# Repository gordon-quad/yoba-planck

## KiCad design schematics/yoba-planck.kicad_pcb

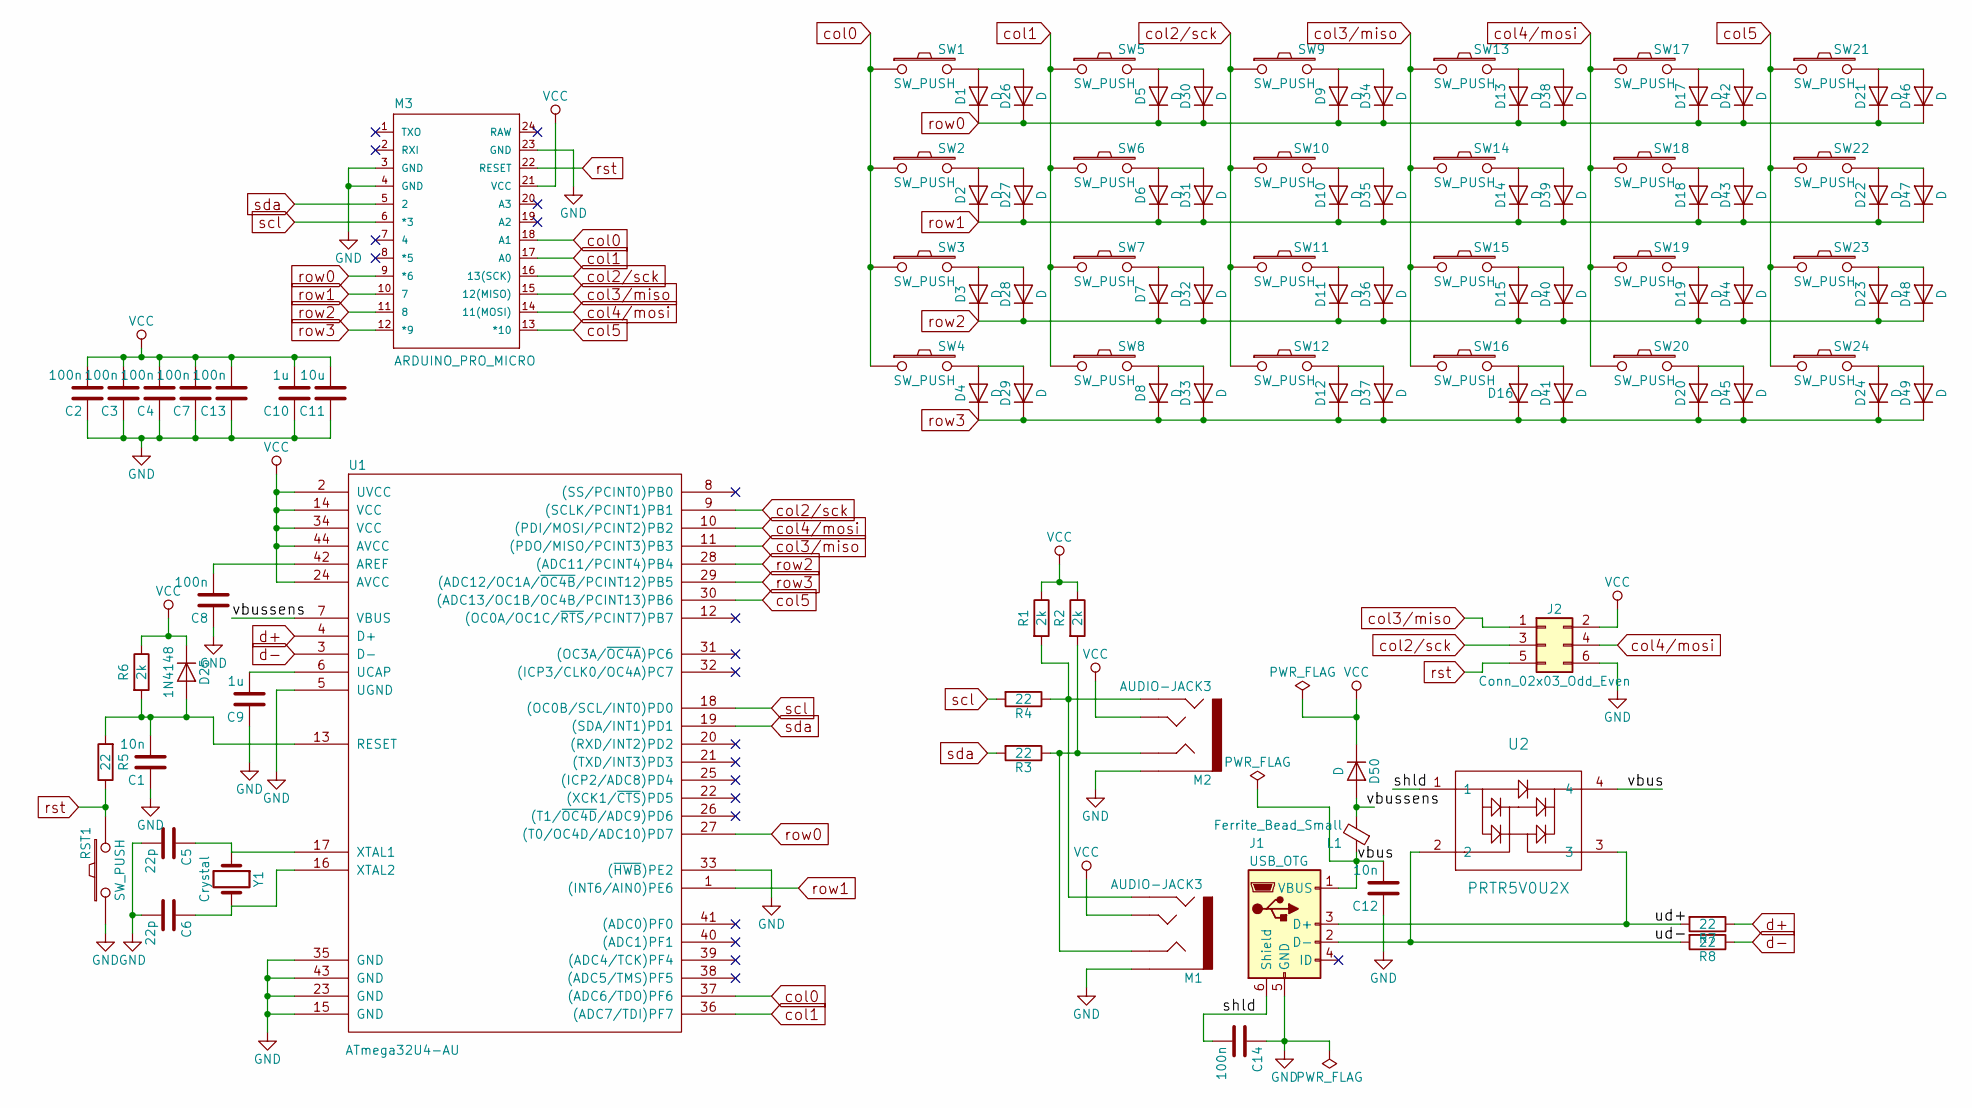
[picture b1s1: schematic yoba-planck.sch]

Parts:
C1, C12: 10n; C_0603_HandSoldering
C2, C3, C4, C7, C8, C13, C14: 100n; C_0603_HandSoldering
C5, C6: 22p; C_0603_HandSoldering
C9, C10: 1u; C_0603_HandSoldering
C11: 10u; C_0805_HandSoldering
D1, D2, D3, D4, D5, D6, D7, D8, D9, D10, D11, D12, D13, D14, D15, D16, D17, D18, D19, D20, D21, D22, D23, D24: D; Diode_DO-35_SOD27_Horizontal_RM10
D25: 1N4148; SOD-123
D26, D27, D28, D29, D30, D31, D32, D33, D34, D35, D36, D37, D38, D39, D40, D41, D42, D43, D44, D45, D46, D47, D48, D49, D50: D; SOD-123
J1: USB_OTG; USB_Micro-B_10103594-0001LF
J2: Conn_02x03_Odd_Even; Pin_Header_Straight_2x03
L1: Ferrite_Bead_Small; C_0603_HandSoldering
M1, M2: AUDIO-JACK3; TRRS-ebay
M3: ARDUINO_PRO_MICRO
R1, R2: 2k; Resistor_SMDuniversal_0805to1206_HandSoldering
R3, R4: 22; Resistor_SMDuniversal_0805to1206_HandSoldering
R5, R7, R8: 22; R_0603_HandSoldering
R6: 2k; R_0603_HandSoldering
RST1: SW_PUSH; edgeswbut
SW1, SW2, SW3, SW4, SW5, SW6, SW7, SW8, SW9, SW10, SW11, SW12, SW13, SW14, SW15, SW16, SW17, SW18, SW19, SW20, SW21, SW22, SW23, SW24: SW_PUSH; MX1A
U1: ATmega32U4-AU; TQFP-44_10x10mm_Pitch0.8mm
U2: PRTR5V0U2X; SOT143B
Y1: Crystal; Crystal_SMD_5032_2Pads

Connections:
/shld: C14.2, J1.6 (Shield), U2.1
/ud+: J1.3 (D+), R7.2, U2.3
/ud-: J1.2 (D-), R8.2, U2.2
/vbus: C12.2, J1.1 (VBUS), L1.1, U2.4
/vbussens: D50.2 (A), L1.2, U1.7 (VBUS)
GND: C1.1, C2.1, C3.1, C4.1, C5.2, C6.2, C7.1, C8.1, C9.1, C10.1, C11.1, C12.1, C13.1, C14.1, J1.5 (GND), J2.6, M1.1 (EARTH), M2.1 (EARTH), M3.3 (GND), M3.4 (GND), M3.23 (GND), RST1.1, U1.5 (UGND), U1.15 (GND), U1.23 (GND), U1.33 ((~HWB~)PE2), U1.35 (GND), U1.43 (GND)
unnamed: C1.2, D25.2 (A), R5.2, R6.2, U1.13 (RESET)
unnamed: C5.1, U1.17 (XTAL1), Y1.1
unnamed: C6.1, U1.16 (XTAL2), Y1.2
unnamed: C8.2, U1.42 (AREF)
unnamed: C9.2, U1.6 (UCAP)
unnamed: D1.2 (A), D26.2 (A), SW1.2
unnamed: D2.2 (A), D27.2 (A), SW2.2
unnamed: D10.2 (A), D35.2 (A), SW10.2
unnamed: D11.2 (A), D36.2 (A), SW11.2
unnamed: D12.2 (A), D37.2 (A), SW12.2
unnamed: D13.2 (A), D38.2 (A), SW13.2
unnamed: D14.2 (A), D39.2 (A), SW14.2
unnamed: D15.2 (A), D40.2 (A), SW15.2
unnamed: D16.2 (A), D41.2 (A), SW16.2
unnamed: D17.2 (A), D42.2 (A), SW17.2
unnamed: D18.2 (A), D43.2 (A), SW18.2
unnamed: D19.2 (A), D44.2 (A), SW19.2
unnamed: D20.2 (A), D45.2 (A), SW20.2
unnamed: D21.2 (A), D46.2 (A), SW21.2
unnamed: D22.2 (A), D47.2 (A), SW22.2
unnamed: D23.2 (A), D48.2 (A), SW23.2
unnamed: D24.2 (A), D49.2 (A), SW24.2
unnamed: D3.2 (A), D28.2 (A), SW3.2
unnamed: D4.2 (A), D29.2 (A), SW4.2
unnamed: D5.2 (A), D30.2 (A), SW5.2
unnamed: D6.2 (A), D31.2 (A), SW6.2
unnamed: D7.2 (A), D32.2 (A), SW7.2
unnamed: D8.2 (A), D33.2 (A), SW8.2
unnamed: D9.2 (A), D34.2 (A), SW9.2
unnamed: M1.2 (RNG2), M2.2 (RNG2), R1.2, R4.1
unnamed: M1.3 (RNG1), M2.3 (RNG1), R2.2, R3.1
VCC: C2.2, C3.2, C4.2, C7.2, C10.2, C11.2, C13.2, D25.1 (K), D50.1 (K), J2.2, M1.4 (TIP), M2.4 (TIP), M3.21 (VCC), R1.1, R2.1, R6.1, U1.2 (UVCC), U1.14 (VCC), U1.24 (AVCC), U1.34 (VCC), U1.44 (AVCC)
col0: M3.18 (A1), SW1.1, SW2.1, SW3.1, SW4.1, U1.37 ((ADC6/TDO)PF6)
col1: M3.17 (A0), SW5.1, SW6.1, SW7.1, SW8.1, U1.36 ((ADC7/TDI)PF7)
col2/sck: J2.3, M3.16 (13(SCK)), SW9.1, SW10.1, SW11.1, SW12.1, U1.9 ((SCLK/PCINT1)PB1)
col3/miso: J2.1, M3.15 (12(MISO)), SW13.1, SW14.1, SW15.1, SW16.1, U1.11 ((PDO/MISO/PCINT3)PB3)
col4/mosi: J2.4, M3.14 (11(MOSI)), SW17.1, SW18.1, SW19.1, SW20.1, U1.10 ((PDI/MOSI/PCINT2)PB2)
col5: M3.13 (*10), SW21.1, SW22.1, SW23.1, SW24.1, U1.30 ((ADC13/OC1B/OC4B/PCINT13)PB6)
d+: R7.1, U1.4 (D+)
d-: R8.1, U1.3 (D-)
row0: D1.1 (K), D5.1 (K), D9.1 (K), D13.1 (K), D17.1 (K), D21.1 (K), D26.1 (K), D30.1 (K), D34.1 (K), D38.1 (K), D42.1 (K), D46.1 (K), M3.9 (*6), U1.27 ((T0/OC4D/ADC10)PD7)
row1: D2.1 (K), D6.1 (K), D10.1 (K), D14.1 (K), D18.1 (K), D22.1 (K), D27.1 (K), D31.1 (K), D35.1 (K), D39.1 (K), D43.1 (K), D47.1 (K), M3.10 (7), U1.1 ((INT6/AIN0)PE6)
row2: D3.1 (K), D7.1 (K), D11.1 (K), D15.1 (K), D19.1 (K), D23.1 (K), D28.1 (K), D32.1 (K), D36.1 (K), D40.1 (K), D44.1 (K), D48.1 (K), M3.11 (8), U1.28 ((ADC11/PCINT4)PB4)
row3: D4.1 (K), D8.1 (K), D12.1 (K), D16.1 (K), D20.1 (K), D24.1 (K), D29.1 (K), D33.1 (K), D37.1 (K), D41.1 (K), D45.1 (K), D49.1 (K), M3.12 (*9), U1.29 ((ADC12/OC1A/~OC4B~/PCINT12)PB5)
rst: J2.5, M3.22 (RESET), R5.1, RST1.2
scl: M3.6 (*3), R4.2, U1.18 ((OC0B/SCL/INT0)PD0)
sda: M3.5 (2), R3.2, U1.19 ((SDA/INT1)PD1)

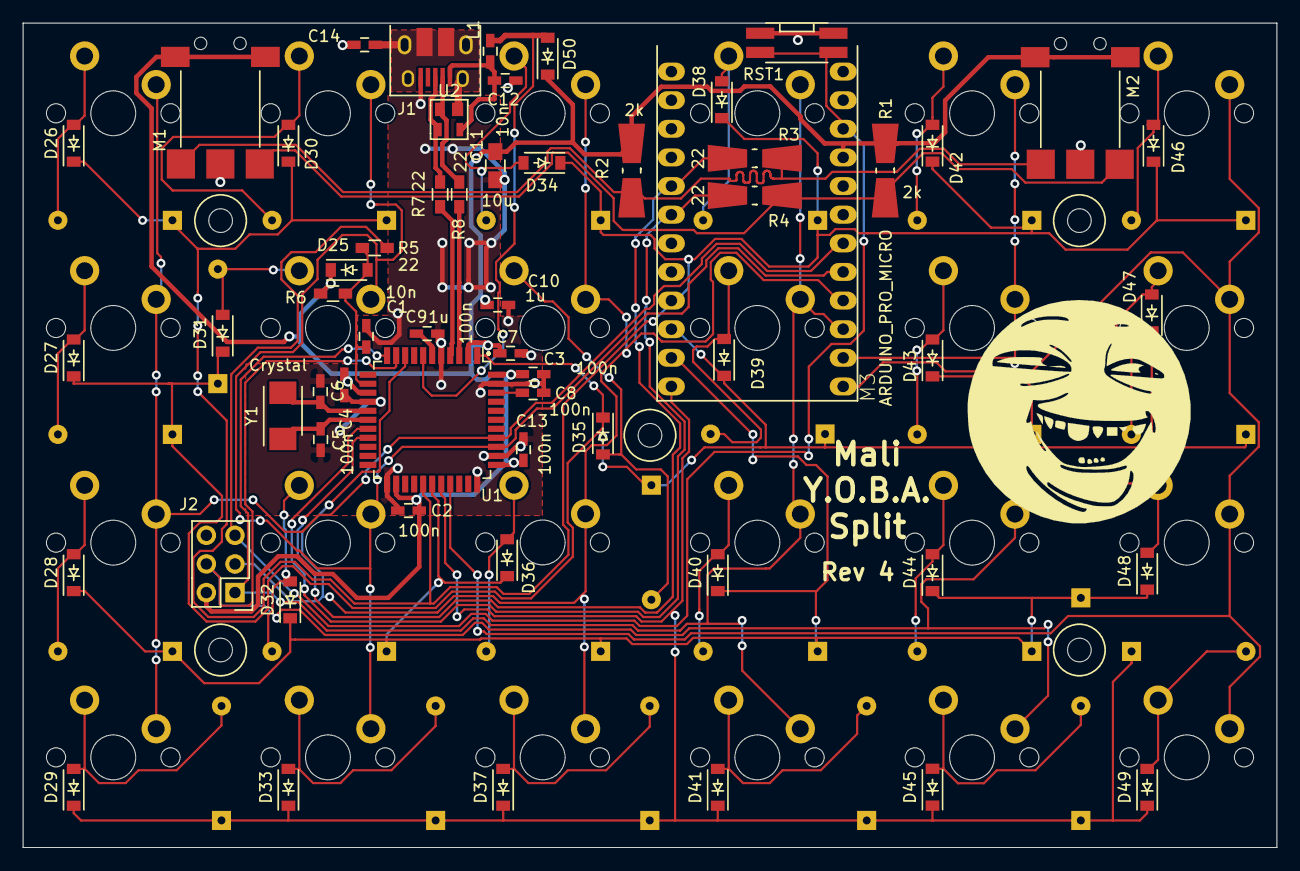
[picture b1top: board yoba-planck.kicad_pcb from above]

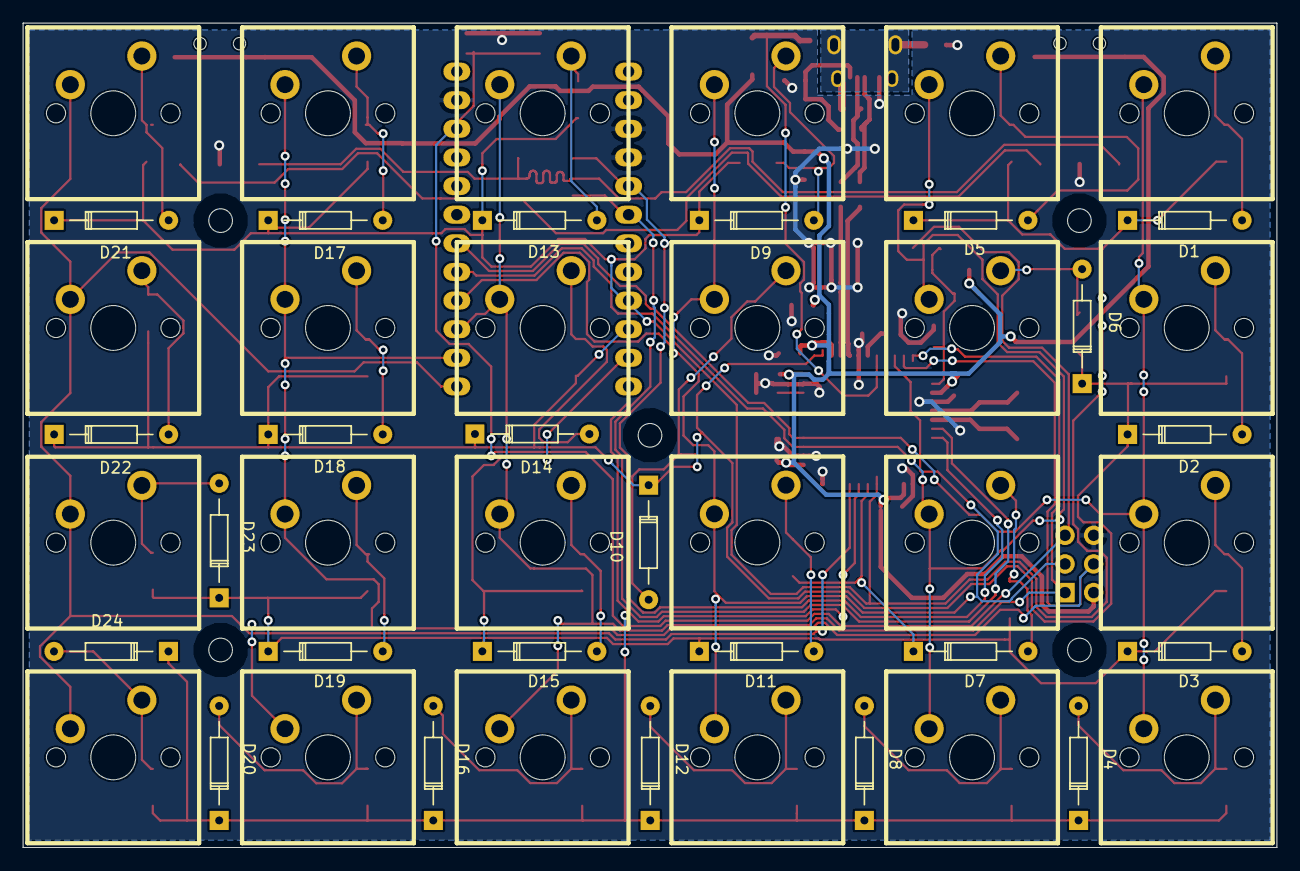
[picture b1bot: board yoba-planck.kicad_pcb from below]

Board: 2 copper layers, 111.2 x 73.2 mm, 106 parts (48 on the bottom side), 53 nets.

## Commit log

2017-03-29 removed silk screen outside board edges
2017-03-29 series resistance added to i2c bus
2017-03-30 Logo updated, layout improoved, mouting holes enlarged
2017-03-30 fixed board outline
2017-05-20 rev2
2017-05-20 case added
2018-02-25 yoba rev3 to smd
2018-03-31 fixed vbus sense line for atmega32u4
